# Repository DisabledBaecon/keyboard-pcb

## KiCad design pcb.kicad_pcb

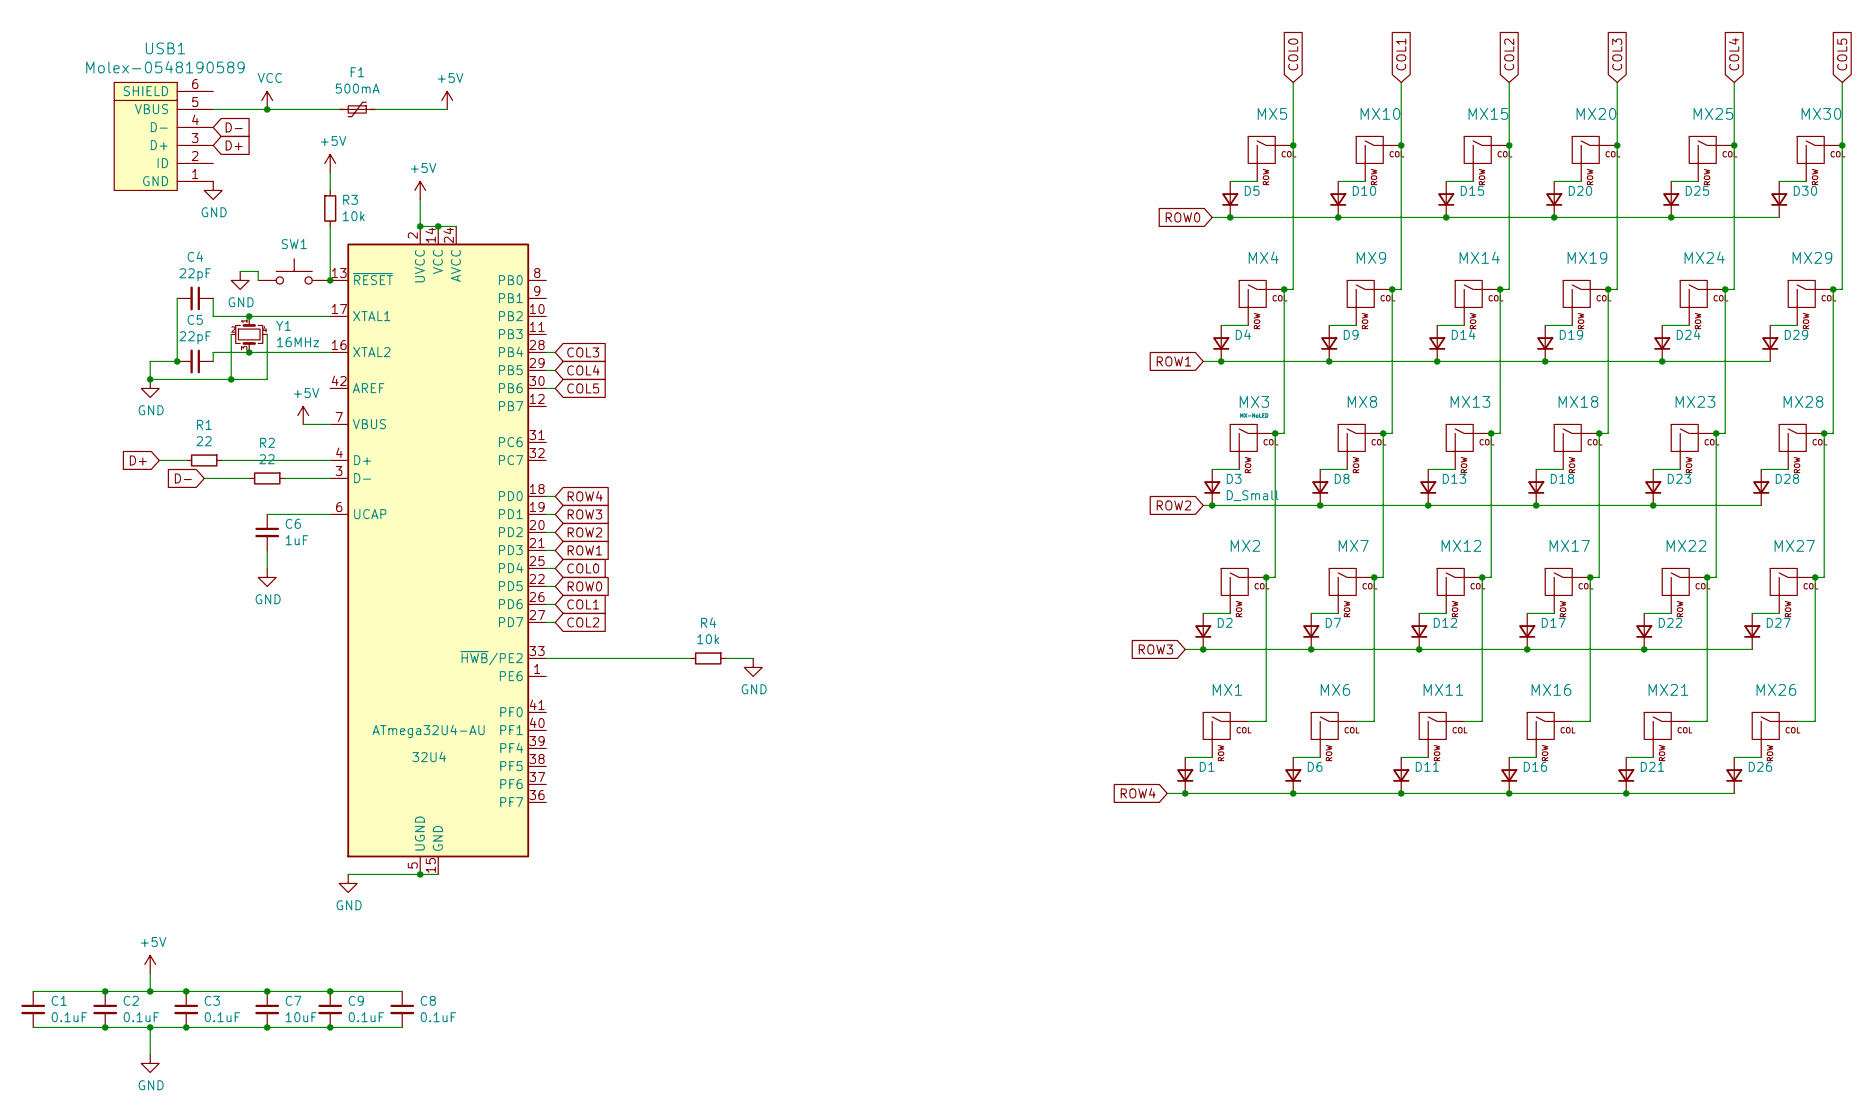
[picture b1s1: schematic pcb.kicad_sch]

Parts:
32U4: ATmega32U4-AU; TQFP-44_10x10mm_P0.8mm
C1, C2, C3, C8, C9: 0.1uF; C_0805_2012Metric
C4, C5: 22pF; C_0805_2012Metric
C6: 1uF; C_0805_2012Metric
C7: 10uF; C_0805_2012Metric
D1, D2, D3, D4, D5, D6, D7, D8, D9, D10, D11, D12, D13, D14, D15, D16, D17, D18, D19, D20, D21, D22, D23, D24, D25, D26, D27, D28, D29, D30: D_Small; D_SOD-123
F1: 500mA; Fuse_1206_3216Metric
MX1, MX2, MX3, MX4, MX5, MX6, MX7, MX8, MX9, MX10, MX11, MX12, MX13, MX14, MX15, MX16, MX17, MX18, MX19, MX20, MX21, MX22, MX23, MX24, MX25, MX26, MX27, MX28, MX29, MX30: MX-NoLED; MXOnly-1U-Hotswap-Modified
R1, R2: 22; R_0805_2012Metric
R3, R4: 10k; R_0805_2012Metric
SW1: SW_Push; SKQG-1155865
USB1: Molex-0548190589
Y1: 16MHz; Crystal_SMD_3225-4Pin_3.2x2.5mm

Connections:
+5V: 32U4.2 (UVCC), 32U4.7 (VBUS), 32U4.14 (VCC), 32U4.24 (AVCC), 32U4.34 (VCC), 32U4.44 (AVCC), C1.1, C2.1, C3.1, C7.1, C8.1, C9.1, F1.1, R3.1
COL0: 32U4.25 (PD4), MX1.1 (COL), MX2.1 (COL), MX3.1 (COL), MX4.1 (COL), MX5.1 (COL)
COL1: 32U4.26 (PD6), MX6.1 (COL), MX7.1 (COL), MX8.1 (COL), MX9.1 (COL), MX10.1 (COL)
COL2: 32U4.27 (PD7), MX11.1 (COL), MX12.1 (COL), MX13.1 (COL), MX14.1 (COL), MX15.1 (COL)
COL3: 32U4.28 (PB4), MX16.1 (COL), MX17.1 (COL), MX18.1 (COL), MX19.1 (COL), MX20.1 (COL)
COL4: 32U4.29 (PB5), MX21.1 (COL), MX22.1 (COL), MX23.1 (COL), MX24.1 (COL), MX25.1 (COL)
COL5: 32U4.30 (PB6), MX26.1 (COL), MX27.1 (COL), MX28.1 (COL), MX29.1 (COL), MX30.1 (COL)
D+: R1.2, USB1.3 (D+)
D-: R2.2, USB1.4 (D-)
GND: 32U4.5 (UGND), 32U4.15 (GND), 32U4.23 (GND), 32U4.35 (GND), 32U4.43 (GND), C1.2, C2.2, C3.2, C4.2, C5.2, C6.2, C7.2, C8.2, C9.2, R4.1, SW1.1, USB1.1 (GND), Y1.2, Y1.4
unnamed: 32U4.3 (D-), R2.1
unnamed: 32U4.4 (D+), R1.1
unnamed: 32U4.6 (UCAP), C6.1
unnamed: 32U4.13 (~RESET), R3.2, SW1.2
unnamed: 32U4.16 (XTAL2), C5.1, Y1.3
unnamed: 32U4.17 (XTAL1), C4.1, Y1.1
unnamed: 32U4.33 (~HWB/PE2), R4.2
unnamed: D1.2 (A), MX1.2 (ROW)
unnamed: D2.2 (A), MX2.2 (ROW)
unnamed: D3.2 (A), MX3.2 (ROW)
unnamed: D4.2 (A), MX4.2 (ROW)
unnamed: D5.2 (A), MX5.2 (ROW)
unnamed: D6.2 (A), MX6.2 (ROW)
unnamed: D7.2 (A), MX7.2 (ROW)
unnamed: D8.2 (A), MX8.2 (ROW)
unnamed: D9.2 (A), MX9.2 (ROW)
unnamed: D10.2 (A), MX10.2 (ROW)
unnamed: D11.2 (A), MX11.2 (ROW)
unnamed: D12.2 (A), MX12.2 (ROW)
unnamed: D13.2 (A), MX13.2 (ROW)
unnamed: D14.2 (A), MX14.2 (ROW)
unnamed: D15.2 (A), MX15.2 (ROW)
unnamed: D16.2 (A), MX16.2 (ROW)
unnamed: D17.2 (A), MX17.2 (ROW)
unnamed: D18.2 (A), MX18.2 (ROW)
unnamed: D19.2 (A), MX19.2 (ROW)
unnamed: D20.2 (A), MX20.2 (ROW)
unnamed: D21.2 (A), MX21.2 (ROW)
unnamed: D22.2 (A), MX22.2 (ROW)
unnamed: D23.2 (A), MX23.2 (ROW)
unnamed: D24.2 (A), MX24.2 (ROW)
unnamed: D25.2 (A), MX25.2 (ROW)
unnamed: D26.2 (A), MX26.2 (ROW)
unnamed: D27.2 (A), MX27.2 (ROW)
unnamed: D28.2 (A), MX28.2 (ROW)
unnamed: D29.2 (A), MX29.2 (ROW)
unnamed: D30.2 (A), MX30.2 (ROW)
ROW0: 32U4.22 (PD5), D5.1 (K), D10.1 (K), D15.1 (K), D20.1 (K), D25.1 (K), D30.1 (K)
ROW1: 32U4.21 (PD3), D4.1 (K), D9.1 (K), D14.1 (K), D19.1 (K), D24.1 (K), D29.1 (K)
ROW2: 32U4.20 (PD2), D3.1 (K), D8.1 (K), D13.1 (K), D18.1 (K), D23.1 (K), D28.1 (K)
ROW3: 32U4.19 (PD1), D2.1 (K), D7.1 (K), D12.1 (K), D17.1 (K), D22.1 (K), D27.1 (K)
ROW4: 32U4.18 (PD0), D1.1 (K), D6.1 (K), D11.1 (K), D16.1 (K), D21.1 (K), D26.1 (K)
VCC: F1.2, USB1.5 (VBUS)

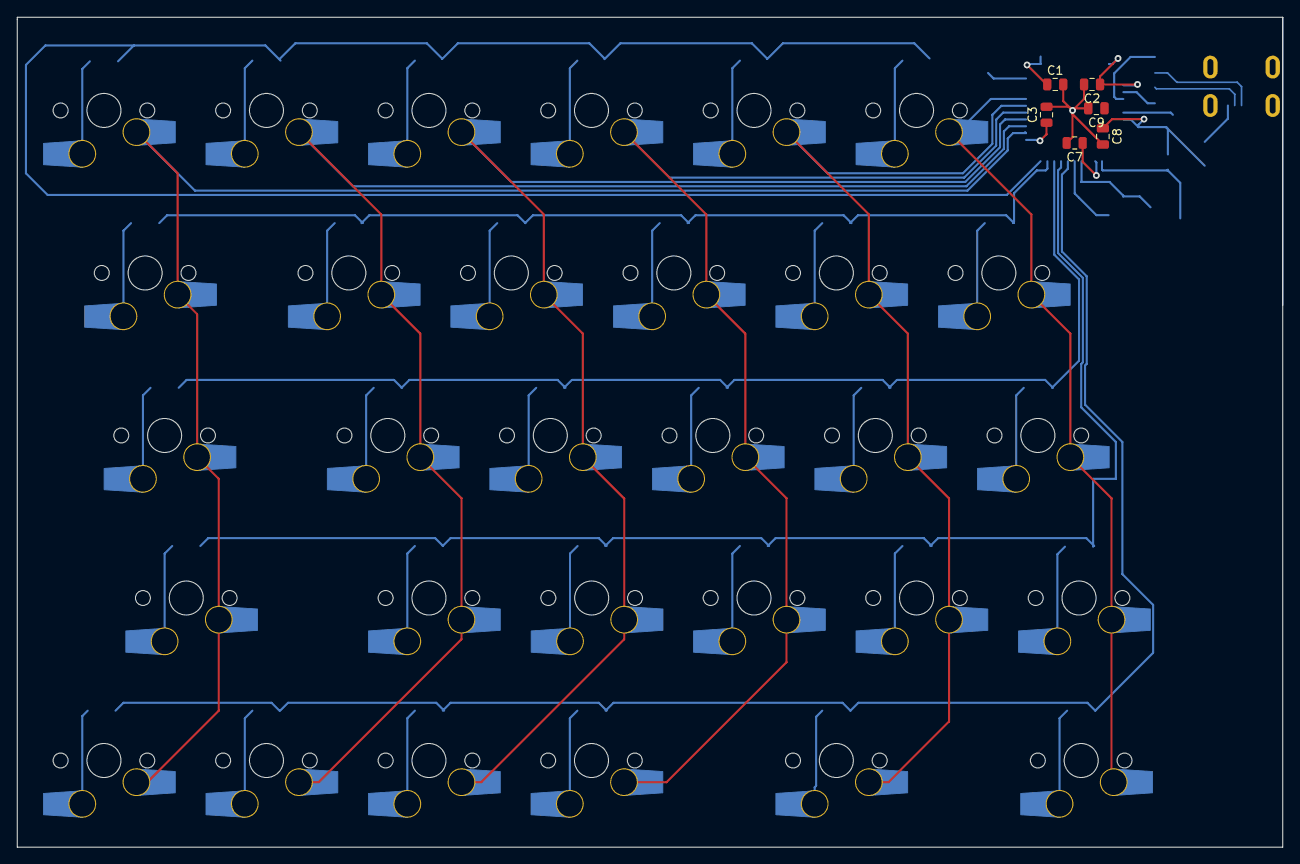
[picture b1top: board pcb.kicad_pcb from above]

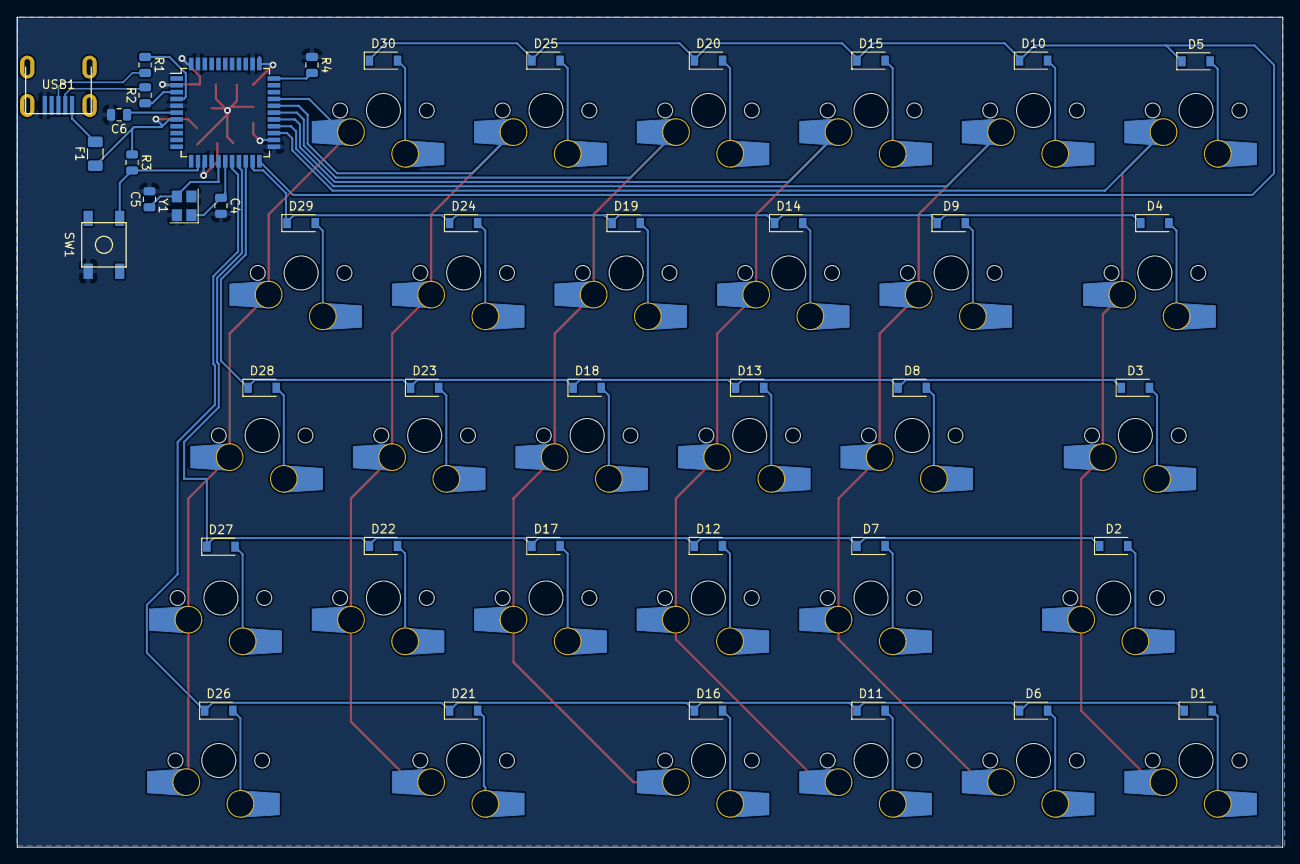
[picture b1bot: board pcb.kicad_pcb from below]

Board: 2 copper layers, 148.3 x 97.3 mm, 78 parts (42 on the bottom side), 53 nets.

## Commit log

2021-04-28 Added default kicad files
2021-04-28 Added Submodules
2021-04-28 Added Libraries
2021-04-28 Basic Build of PCB Schematic
2021-04-28 Added Switch Matrix
2021-04-28 Added footprint for all components
2021-04-28 Set Rows and Columns to 32u4 Pins
2021-04-28 Updated Row Pinout
2021-04-28 Moved Things Around
    Still not sure this is any good
2021-04-28 Updated PCB from Schematic
2021-04-30 Added Layout.png
2021-06-28 Made Changes
    idk
2021-11-23 No idea
    No clue what's changed
2022-11-23 Attempt 1
    Attempt 1
2022-11-23 Tidied Schematic
    Removed Lines, replaced with tags
2022-11-24 Tracing
    Traces for diodes done. Switch traces started
2022-11-24 Routing Cont
    Routing between switches and diodes v0.1 done
2022-11-24 Made A Mess
    Made A Mess
2022-11-24 No clue what I did
2022-11-24 Added GND Zone
    Added GND Zone
2022-11-25 Unknown
    Unknown
2022-11-28 Cleaned PCB
    Added hotswap, started new trace routes
2022-11-28 V0.2
    Replaced Footprint. Trace Routes (almost) done
2022-11-29 ...
    ...
2022-11-29 Spaghetti Junction
    Yummm
2022-11-29 backups
    backups added
2022-12-04 Unknown Changes
2022-12-14 backup
